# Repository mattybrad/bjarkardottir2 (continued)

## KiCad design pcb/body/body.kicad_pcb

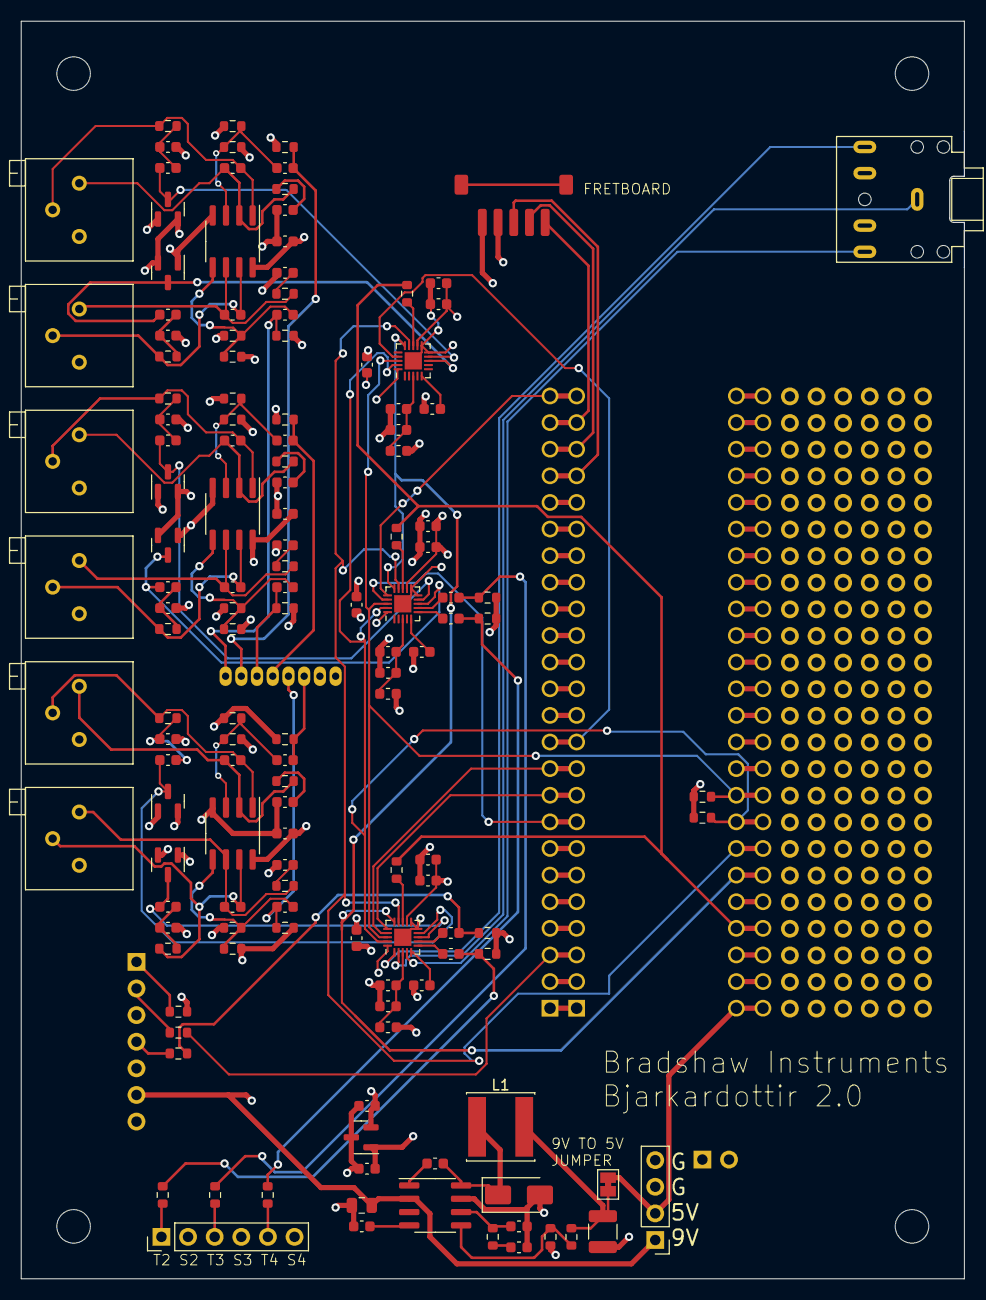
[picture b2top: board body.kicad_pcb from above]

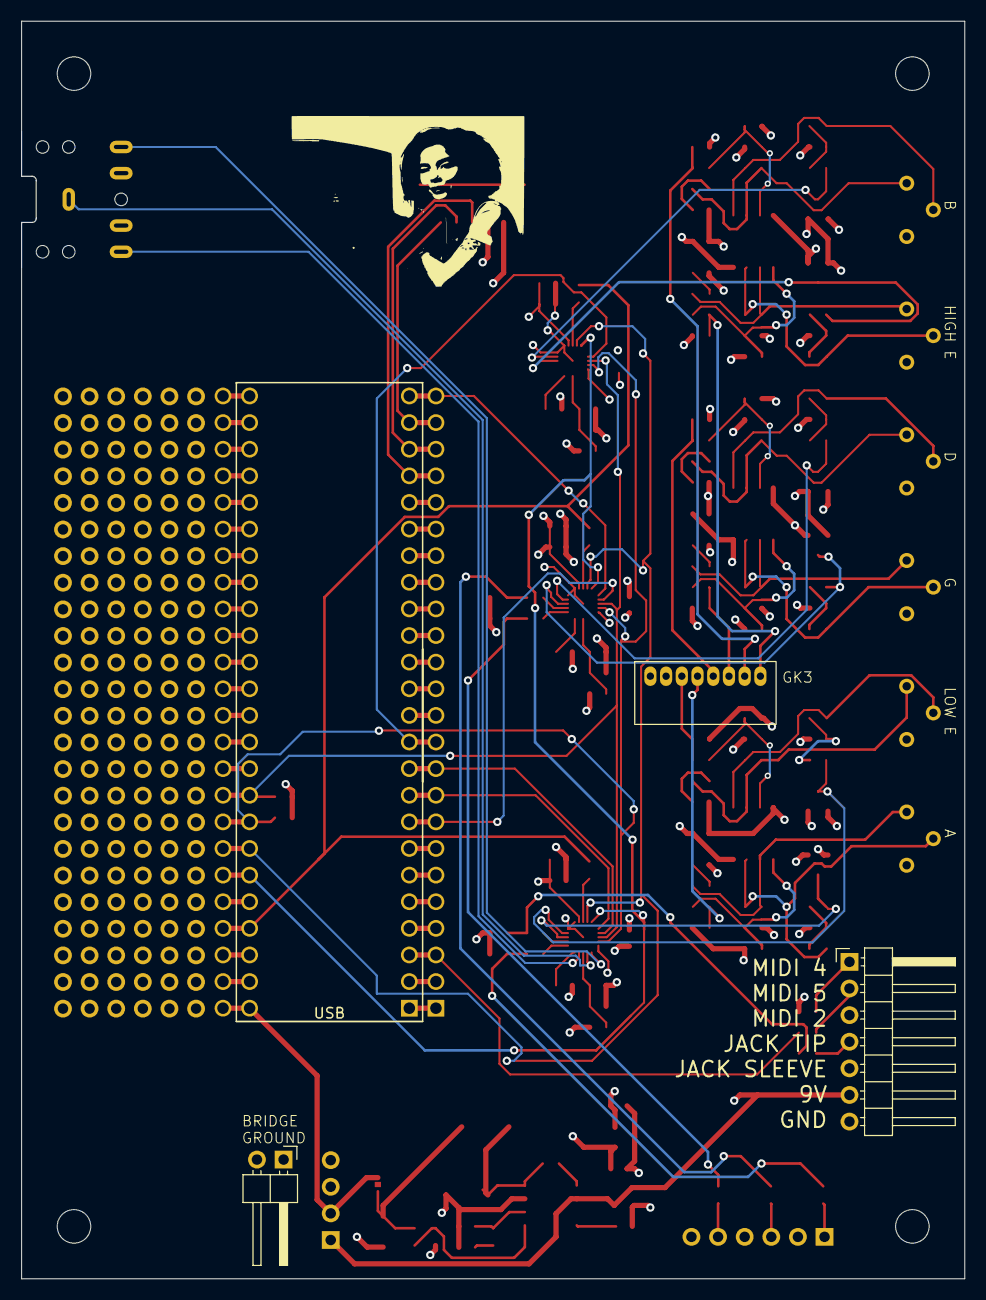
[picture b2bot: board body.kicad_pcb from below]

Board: 4 copper layers, 90.0 x 120.0 mm, 293 parts (4 on the bottom side), 94 nets.

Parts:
C1, C2, C3, C4: 1uF; C_0603_1608Metric
C5, C6, C16, C17, C27, C28: 0.1u; C_0603_1608Metric
C7, C8, C18, C19, C29, C30: 10u; C_0603_1608Metric
C9, C10, C20, C21, C31, C32: 18p; C_0603_1608Metric
C11, C22, C33: 100n; C_0603_1608Metric
C12, C13, C23, C24, C34, C35: 1n; C_0603_1608Metric
C14, C15, C25, C26, C36, C37, C60, C62: 1u; C_0603_1608Metric
C38, C40, C42, C44, C46, C48, C50, C52, C54: 2.2uF; C_0603_1608Metric
C39, C43, C45, C49, C51, C55: 0.1uF; C_0603_1608Metric
C41, C47, C53: 0.15uF; C_0603_1608Metric
C56: 22uF 16V; C_0805_2012Metric
C57: 100nF; C_0603_1608Metric
C58: 10nF; C_0603_1608Metric
C59: 1nF; C_0603_1608Metric
C61: 10pF; C_0603_1608Metric
C63: 47uF; C_1210_3225Metric
D1, D2, D3, D4, D5, D6: BAT54S; SOT-23
D7: B340A; D_SMA
FB1, FB2, FB3: 600; L_0603_1608Metric
H1, H2, H3, H4: MountingHole; MountingHole_3.2mm_M3
J1: FRETBOARD_CONNECTION; jst zh fretboard connector
J2: BRIDGE_GROUND; PinHeader_1x02_P2.54mm_Horizontal
J3: GK3_socket; gk3 connector THT
J4: AudioJack3_SwitchTR; Jack_3.5mm_CUI_SJ1-3525N_Horizontal
J5: External_connections; PinHeader_1x07_P2.54mm_Horizontal
J6: OUTPUTS_234; PinHeader_1x06_P2.54mm_Vertical
J7: Battery_Power; PinHeader_1x04_P2.54mm_Vertical
JP1: Jumper_2_Bridged; SolderJumper-2_P1.3mm_Bridged_Pad1.0x1.5mm
L1: 6.8uH; L_Sunlord_SWPA6045S
PB1, PB2, PB3, PB4, PB5, PB6, PB7, PB8, PB9, PB10, PB11, PB12, PB13, PB14, PB15, PB16, PB17, PB18, PB19, PB20, PB21, PB22, PB23, PB24, PB25, PB26, PB27, PB28, PB29, PB30, PB31, PB32, PB33, PB34, PB35, PB36, PB37, PB38, PB39, PB40, PB41, PB42, PB43, PB44, PB45, PB46, PB47, PB48, PB49, PB50, PB51, PB52, PB53, PB54, PB55, PB56, PB57, PB58, PB59, PB60, PB61, PB62, PB63, PB64, PB65, PB66, PB67, PB68, PB69, PB70, PB71, PB72, PB73, PB74, PB75, PB76, PB77, PB78, PB79, PB80, PB81, PB82, PB83, PB84, PB85, PB86, PB87, PB88, PB89, PB90, PB91, PB92, PB93, PB94, PB95, PB96, PB97, PB98, PB99, PB100, PB101, PB102, PB103, PB104, PB105, PB106, PB107, PB108, PB109, PB110, PB111, PB112, PB113, PB114, PB115, PB116, PB117, PB118, PB119, PB120, PB121, PB122, PB123, PB124, PB125, PB126, PB127, PB128, PB129, PB130, PB131, PB132, PB133, PB134, PB135, PB136, PB137, PB138, PB139, PB140, PB141, PB142, PB143, PB144: perfboard_pin; perfboard pin
R1, R2: 2.2k; R_0603_1608Metric
R3, R4, R6, R7: 47k; R_0603_1608Metric
R5, R8: 47R; R_0603_1608Metric
R9, R10, R11, R12: 100R; R_0603_1608Metric
R13, R14, R23, R24, R33, R34: 1M; R_0603_1608Metric
R15, R16, R17, R18, R25, R26, R27, R28, R35, R36, R37, R38: 2M; R_0603_1608Metric
R19, R20, R29, R30, R39, R40, R47: 10k; R_0603_1608Metric
R21, R22, R31, R32, R41, R42: 1k; R_0603_1608Metric
R43, R44, R45: 100; R_0603_1608Metric
R46: 50k; R_0603_1608Metric
R48: 1.8k; R_0603_1608Metric
RV1, RV2, RV3, RV4, RV5, RV6: 10k; Potentiometer_Bourns_3296P_Horizontal
U1: Teensy4.1; Teensy41_breakout
U2, U3, U4: TL072; SOIC-8_3.9x4.9mm_P1.27mm
U5, U6, U7: SGTL5000XNLA3; QFN-20-1EP_3x3mm_P0.4mm_EP1.65x1.65mm
U8: TPS54331DR; SOIC-8_3.9x4.9mm_P1.27mm
U9: AP7313-18SAG; SOT-23

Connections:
+1V8: C40.1, C46.1, C52.1, C62.1, U5.20 (VDDD), U6.20 (VDDD), U7.20 (VDDD), U9.2 (VO)
+3.3V: C38.1, C39.1, C44.1, C45.1, C50.1, C51.1, C60.1, D1.2 (K), D2.2 (K), D3.2 (K), D4.2 (K), D5.2 (K), D6.2 (K), FB1.1, FB2.1, FB3.1, J1.1, R1.2, R2.2, R5.1, U1.15 (3V3), U1.46 (3V3), U5.12 (VDDIO), U6.12 (VDDIO), U7.12 (VDDIO), U9.1 (VI)
+5V: J7.2, JP1.2 (B), U1.48 (VIN)
+9V: C11.2, C22.2, C33.2, C56.1, J5.6, J7.1, R15.1, R17.1, R25.1, R27.1, R35.1, R37.1, U2.8 (V+), U3.8 (V+), U4.8 (V+), U8.2 (VIN)
/MIDI_PIN_4: J5.1, R5.2
/MIDI_PIN_5: J5.2, R8.2
/codec1/HEADPHONES_GND: J4.S, U5.2 (HP_VGND)
/codec1/HEADPHONES_L: J4.T, U5.1 (HP_R)
/codec1/HEADPHONES_R: J4.R, U5.4 (HP_L)
/codec1/LINE_IN_L: C14.1, D1.3 (COM), U5.9 (LINEIN_L)
/codec1/LINE_IN_R: C15.1, D2.3 (COM), U5.8 (LINEIN_R)
/codec1/LINE_OUT_L: C1.1, U5.7 (LINEOUT_L)
/codec1/LINE_OUT_R: C2.1, U5.6 (LINEOUT_R)
/codec2/LINE_IN_L: C25.1, D3.3 (COM), U6.9 (LINEIN_L)
/codec2/LINE_IN_R: C26.1, D4.3 (COM), U6.8 (LINEIN_R)
/codec2/LINE_OUT_L: C3.1, U6.7 (LINEOUT_L)
/codec2/LINE_OUT_R: C4.1, U6.6 (LINEOUT_R)
/codec3/LINE_IN_L: C36.1, D5.3 (COM), U7.9 (LINEIN_L)
/codec3/LINE_IN_R: C37.1, D6.3 (COM), U7.8 (LINEIN_R)
/pickuppair1/INPUT_1: C5.1, J3.3, R13.1
/pickuppair1/INPUT_2: C6.1, J3.4, R14.1
/pickuppair2/INPUT_1: C16.1, J3.5, R23.1
/pickuppair2/INPUT_2: C17.1, J3.6, R24.1
/pickuppair3/INPUT_1: C27.1, J3.7, R33.1
/pickuppair3/INPUT_2: C28.1, J3.8, R34.1
CODEC1_DIN: U1.10 (8_TX2_IN1), U5.17 (I2S_DIN)
CODEC1_DOUT: U1.9 (7_RX2_OUT1A), U5.16 (I2S_DOUT)
CODEC2_DIN: U1.8 (6_OUT1D), U6.17 (I2S_DIN)
CODEC2_DOUT: U1.24 (32_OUT1B), U6.16 (I2S_DOUT)
CODEC3_DIN: U1.11 (9_OUT1C), U7.17 (I2S_DIN)
DAC_BCLK: U1.43 (21_A7_RX5_BCLK1), U5.15 (I2S_SCLK), U6.15 (I2S_SCLK), U7.15 (I2S_SCLK)
DAC_LRCLK: U1.42 (20_A6_TX5_LRCLK1), U5.14 (I2S_LRCLK), U6.14 (I2S_LRCLK), U7.14 (I2S_LRCLK)
DAC_MCLK: R43.2, R44.2, R45.2, U1.45 (23_A9_CRX1_MCLK1)
DAC_SCL: R1.1, U1.41 (19_A5_SCL), U5.19 (CTRL_CLK), U6.19 (CTRL_CLK), U7.19 (CTRL_CLK)
DAC_SDA: R2.1, U1.40 (18_A4_SDA), U5.18 (CTRL_DATA), U6.18 (CTRL_DATA), U7.18 (CTRL_DATA)
FRET_CLOCK: J1.3, U1.21 (29_TX7)
FRET_DATA: J1.5, U1.23 (31_CTX3)
FRET_LOAD: J1.4, U1.22 (30_CRX3)
GND: C7.1, C8.1, C11.1, C12.2, C13.2, C18.1, C19.1, C22.1, C23.2, C24.2, C29.1, C30.1, C33.1, C34.2, C35.2, C38.2, C39.2, C40.2, C41.2, C42.2, C43.2, C44.2, C45.2, C46.2, C47.2, C48.2, C49.2, C50.2, C51.2, C52.2, C53.2, C54.2, C55.2, C56.2, C58.2, C59.2, C60.2, C61.2, C62.2, C63.2, D1.1 (A), D2.1 (A), D3.1 (A), D4.1 (A), D5.1 (A), D6.1 (A), D7.2 (A), J1.2, J2.1, J2.2, J3.1, J3.2, J5.3, J5.5, J5.7, J6.2, J6.4, J6.6, J7.3, J7.4, R3.1, R4.1, R6.1, R7.1, R13.2, R14.2, R16.2, R18.2, R23.2, R24.2, R26.2, R28.2, R33.2, R34.2, R36.2, R38.2, R48.2, U1.1 (GND), U1.34 (GND), U1.47 (GND), U2.4 (V-), U3.4 (V-), U4.4 (V-), U5.10 (MIC), U5.11 (MIC_BIAS), U5.21 (GND), U6.10 (MIC), U6.11 (MIC_BIAS), U6.21 (GND), U7.10 (MIC), U7.11 (MIC_BIAS), U7.21 (GND), U8.7 (GND), U9.3 (GND)
MAIN_OUTPUT: J5.4, R9.1
MIDI_OUT: R8.1, U1.3 (1_TX1_CTX2_MISO1)
unnamed: C1.2, R6.2, R9.2
unnamed: C2.2, R3.2, R10.2
unnamed: C3.2, R7.2, R11.2
unnamed: C4.2, R4.2, R12.2
unnamed: C7.2, R19.1
unnamed: C8.2, R20.1
unnamed: C9.2, R21.1, RV1.2, U2.1
unnamed: C10.2, R22.1, RV2.2, U2.7
unnamed: C12.1, C14.2, R21.2
unnamed: C13.1, C15.2, R22.2
unnamed: C18.2, R29.1
unnamed: C19.2, R30.1
unnamed: C20.2, R31.1, RV3.2, U3.1
unnamed: C21.2, R32.1, RV4.2, U3.7
unnamed: C23.1, C25.2, R31.2
unnamed: C24.1, C26.2, R32.2
unnamed: C29.2, R39.1
unnamed: C30.2, R40.1
unnamed: C31.2, R41.1, RV5.2, U4.1
unnamed: C32.2, R42.1, RV6.2, U4.7
unnamed: C34.1, C36.2, R41.2
unnamed: C35.1, C37.2, R42.2
unnamed: C59.1, R46.2
unnamed: C57.1, D7.1 (K), L1.1, U8.8 (PH)
unnamed: J6.1, R10.1
unnamed: J6.3, R11.1
unnamed: J6.5, R12.1
unnamed: C63.1, JP1.1 (A), L1.2, R47.1
unnamed: C5.2, R15.2, R16.1, U2.3 (+)
unnamed: C9.1, R19.2, RV1.1, U2.2 (-)
unnamed: C6.2, R17.2, R18.1, U2.5 (+)
unnamed: C10.1, R20.2, RV2.1, U2.6 (-)
unnamed: C16.2, R25.2, R26.1, U3.3 (+)
unnamed: C20.1, R29.2, RV3.1, U3.2 (-)
unnamed: C17.2, R27.2, R28.1, U3.5 (+)
unnamed: C21.1, R30.2, RV4.1, U3.6 (-)
unnamed: C27.2, R35.2, R36.1, U4.3 (+)
unnamed: C31.1, R39.2, RV5.1, U4.2 (-)
unnamed: C28.2, R37.2, R38.1, U4.5 (+)
unnamed: C32.1, R40.2, RV6.1, U4.6 (-)
unnamed: R43.1, U5.13 (SYS_MCLK)
unnamed: C41.1, U5.5 (VAG)
unnamed: C42.1, C43.1, FB1.2, U5.3 (VDDA)
unnamed: R44.1, U6.13 (SYS_MCLK)
unnamed: C47.1, U6.5 (VAG)
unnamed: C48.1, C49.1, FB2.2, U6.3 (VDDA)
unnamed: R45.1, U7.13 (SYS_MCLK)
unnamed: C53.1, U7.5 (VAG)
unnamed: C54.1, C55.1, FB3.2, U7.3 (VDDA)
unnamed: C57.2, U8.1 (BOOT)
unnamed: C61.1, R46.1, U8.6 (COMP)
unnamed: C58.1, U8.4 (SS)
unnamed: R47.2, R48.1, U8.5 (VSENSE)

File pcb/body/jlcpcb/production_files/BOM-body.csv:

Comment,Designator,Footprint,LCSC
600,"FB1,FB2,FB3",L_0603_1608Metric,C1002
100n,"C11,C16,C17,C22,C27,C28,C33,C39,C43,C45,C49,C5,C51,C55,C57,C6",C_0603_1608Metric,C14663
1uF,"C1,C14,C15,C2,C25,C26,C3,C36,C37,C4,C60,C62",C_0603_1608Metric,C15849
1n,"C12,C13,C23,C24,C34,C35,C59",C_0603_1608Metric,C1588
10nF,"C58,C61",C_0603_1608Metric,C1634
18p,"C10,C20,C21,C31,C32,C9",C_0603_1608Metric,C1647
1k,"R21,R22,R31,R32,R41,R42",R_0603_1608Metric,C21190
100R,"R10,R11,R12,R43,R44,R45,R9",R_0603_1608Metric,C22775
1M,"R13,R14,R23,R24,R33,R34",R_0603_1608Metric,C22935
2M,"R15,R16,R17,R18,R25,R26,R27,R28,R35,R36,R37,R38",R_0603_1608Metric,C22976
47R,"R5,R8",R_0603_1608Metric,C23182
50k,R46,R_0603_1608Metric,C23184
2.2uF,"C38,C40,C42,C44,C46,C48,C50,C52,C54",C_0603_1608Metric,C23630
10k,"R19,R20,R29,R30,R39,R40,R47",R_0603_1608Metric,C25804
47k,"R3,R4,R6,R7",R_0603_1608Metric,C25819
SGTL5000XNLA3,"U5,U6,U7",QFN-20-1EP_3x3mm_P0.4mm_EP1.65x1.65mm,C2651833
B340A,D7,D_SMA,C3018525
1.8k,R48,R_0603_1608Metric,C4177
2.2k,"R1,R2",R_0603_1608Metric,C4190
22uF 16V,C56,C_0805_2012Metric,C45783
AP7313-18SAG,U9,SOT-23,C460373
FRETBOARD_CONNECTION,J1,jst zh fretboard connector,C485355
0.15uF,"C41,C47,C53",C_0603_1608Metric,C513735
6.8uH,L1,L_Sunlord_SWPA6045S,C57254
TL072,"U2,U3,U4",SOIC-8_3.9x4.9mm_P1.27mm,C6961
47uF,C63,C_1210_3225Metric,C89147
BAT54S,"D1,D2,D3,D4,D5,D6",SOT-23,C916425
10u,"C18,C19,C29,C30,C7,C8",C_0603_1608Metric,C96446
TPS54331DR,U8,SOIC-8_3.9x4.9mm_P1.27mm,C9865
perfboard_pin,PB144,perfboard pin,
perfboard_pin,PB143,perfboard pin,
perfboard_pin,PB142,perfboard pin,
perfboard_pin,PB141,perfboard pin,
perfboard_pin,PB140,perfboard pin,
perfboard_pin,PB139,perfboard pin,
perfboard_pin,PB138,perfboard pin,
perfboard_pin,PB137,perfboard pin,
perfboard_pin,PB136,perfboard pin,
perfboard_pin,PB135,perfboard pin,
perfboard_pin,PB134,perfboard pin,
perfboard_pin,PB133,perfboard pin,
perfboard_pin,PB132,perfboard pin,
perfboard_pin,PB131,perfboard pin,
perfboard_pin,PB130,perfboard pin,
perfboard_pin,PB129,perfboard pin,
perfboard_pin,PB128,perfboard pin,
perfboard_pin,PB127,perfboard pin,
perfboard_pin,PB126,perfboard pin,
perfboard_pin,PB125,perfboard pin,
perfboard_pin,PB124,perfboard pin,
perfboard_pin,PB123,perfboard pin,
perfboard_pin,PB122,perfboard pin,
perfboard_pin,PB121,perfboard pin,
perfboard_pin,PB120,perfboard pin,
perfboard_pin,PB119,perfboard pin,
perfboard_pin,PB118,perfboard pin,
perfboard_pin,PB117,perfboard pin,
perfboard_pin,PB116,perfboard pin,
perfboard_pin,PB115,perfboard pin,
perfboard_pin,PB114,perfboard pin,
perfboard_pin,PB113,perfboard pin,
perfboard_pin,PB112,perfboard pin,
perfboard_pin,PB111,perfboard pin,
perfboard_pin,PB110,perfboard pin,
perfboard_pin,PB109,perfboard pin,
perfboard_pin,PB108,perfboard pin,
perfboard_pin,PB107,perfboard pin,
perfboard_pin,PB106,perfboard pin,
perfboard_pin,PB105,perfboard pin,
perfboard_pin,PB104,perfboard pin,
perfboard_pin,PB103,perfboard pin,
perfboard_pin,PB102,perfboard pin,
perfboard_pin,PB101,perfboard pin,
perfboard_pin,PB100,perfboard pin,
perfboard_pin,PB99,perfboard pin,
perfboard_pin,PB98,perfboard pin,
perfboard_pin,PB97,perfboard pin,
perfboard_pin,PB96,perfboard pin,
perfboard_pin,PB95,perfboard pin,
perfboard_pin,PB94,perfboard pin,
perfboard_pin,PB93,perfboard pin,
perfboard_pin,PB92,perfboard pin,
perfboard_pin,PB91,perfboard pin,
perfboard_pin,PB90,perfboard pin,
perfboard_pin,PB89,perfboard pin,
perfboard_pin,PB88,perfboard pin,
perfboard_pin,PB87,perfboard pin,
perfboard_pin,PB86,perfboard pin,
perfboard_pin,PB85,perfboard pin,
perfboard_pin,PB84,perfboard pin,
perfboard_pin,PB83,perfboard pin,
perfboard_pin,PB82,perfboard pin,
perfboard_pin,PB81,perfboard pin,
perfboard_pin,PB80,perfboard pin,
perfboard_pin,PB79,perfboard pin,
perfboard_pin,PB78,perfboard pin,
perfboard_pin,PB77,perfboard pin,
perfboard_pin,PB76,perfboard pin,
perfboard_pin,PB75,perfboard pin,
perfboard_pin,PB74,perfboard pin,
perfboard_pin,PB73,perfboard pin,
perfboard_pin,PB72,perfboard pin,
perfboard_pin,PB71,perfboard pin,
perfboard_pin,PB70,perfboard pin,
perfboard_pin,PB69,perfboard pin,
perfboard_pin,PB68,perfboard pin,
perfboard_pin,PB67,perfboard pin,
perfboard_pin,PB66,perfboard pin,
perfboard_pin,PB65,perfboard pin,
perfboard_pin,PB64,perfboard pin,
perfboard_pin,PB63,perfboard pin,
perfboard_pin,PB62,perfboard pin,
perfboard_pin,PB61,perfboard pin,
perfboard_pin,PB60,perfboard pin,
perfboard_pin,PB59,perfboard pin,
perfboard_pin,PB58,perfboard pin,
perfboard_pin,PB57,perfboard pin,
perfboard_pin,PB56,perfboard pin,
perfboard_pin,PB55,perfboard pin,
perfboard_pin,PB54,perfboard pin,
perfboard_pin,PB53,perfboard pin,
perfboard_pin,PB52,perfboard pin,
perfboard_pin,PB51,perfboard pin,
perfboard_pin,PB50,perfboard pin,
perfboard_pin,PB49,perfboard pin,
perfboard_pin,PB48,perfboard pin,
perfboard_pin,PB47,perfboard pin,
perfboard_pin,PB46,perfboard pin,
perfboard_pin,PB45,perfboard pin,
perfboard_pin,PB44,perfboard pin,
perfboard_pin,PB43,perfboard pin,
perfboard_pin,PB42,perfboard pin,
perfboard_pin,PB41,perfboard pin,
perfboard_pin,PB40,perfboard pin,
perfboard_pin,PB39,perfboard pin,
perfboard_pin,PB38,perfboard pin,
perfboard_pin,PB37,perfboard pin,
perfboard_pin,PB36,perfboard pin,
perfboard_pin,PB35,perfboard pin,
perfboard_pin,PB34,perfboard pin,
perfboard_pin,PB33,perfboard pin,
perfboard_pin,PB32,perfboard pin,
perfboard_pin,PB31,perfboard pin,
perfboard_pin,PB30,perfboard pin,
perfboard_pin,PB29,perfboard pin,
perfboard_pin,PB28,perfboard pin,
perfboard_pin,PB27,perfboard pin,
perfboard_pin,PB26,perfboard pin,
perfboard_pin,PB25,perfboard pin,
perfboard_pin,PB24,perfboard pin,
perfboard_pin,PB23,perfboard pin,
perfboard_pin,PB22,perfboard pin,
perfboard_pin,PB21,perfboard pin,
perfboard_pin,PB20,perfboard pin,
perfboard_pin,PB19,perfboard pin,
perfboard_pin,PB18,perfboard pin,
perfboard_pin,PB17,perfboard pin,
perfboard_pin,PB16,perfboard pin,
perfboard_pin,PB15,perfboard pin,
perfboard_pin,PB14,perfboard pin,
perfboard_pin,PB13,perfboard pin,
perfboard_pin,PB12,perfboard pin,
perfboard_pin,PB11,perfboard pin,
perfboard_pin,PB10,perfboard pin,
perfboard_pin,PB9,perfboard pin,
perfboard_pin,PB8,perfboard pin,
perfboard_pin,PB7,perfboard pin,
perfboard_pin,PB6,perfboard pin,
perfboard_pin,PB5,perfboard pin,
perfboard_pin,PB4,perfboard pin,
perfboard_pin,PB3,perfboard pin,
perfboard_pin,PB2,perfboard pin,
perfboard_pin,PB1,perfboard pin,
GK3_socket,J3,gk3 connector THT,
Jumper_2_Bridged,JP1,SolderJumper-2_P1.3mm_Bridged_Pad1.0x1.5mm,
10k,RV6,Potentiometer_Bourns_3296P_Horizontal,
OUTPUTS_234,J6,PinHeader_1x06_P2.54mm_Vertical,
Battery_Power,J7,PinHeader_1x04_P2.54mm_Vertical,
MountingHole,H3,MountingHole_3.2mm_M3,
10k,RV4,Potentiometer_Bourns_3296P_Horizontal,
MountingHole,H1,MountingHole_3.2mm_M3,
10k,RV1,Potentiometer_Bourns_3296P_Horizontal,
10k,RV3,Potentiometer_Bourns_3296P_Horizontal,
10k,RV2,Potentiometer_Bourns_3296P_Horizontal,
MountingHole,H4,MountingHole_3.2mm_M3,
10k,RV5,Potentiometer_Bourns_3296P_Horizontal,
MountingHole,H2,MountingHole_3.2mm_M3,
AudioJack3_SwitchTR,J4,Jack_3.5mm_CUI_SJ1-3525N_Horizontal,
External_connections,J5,PinHeader_1x07_P2.54mm_Horizontal,
BRIDGE_GROUND,J2,PinHeader_1x02_P2.54mm_Horizontal,
Teensy4.1,U1,Teensy41_breakout,

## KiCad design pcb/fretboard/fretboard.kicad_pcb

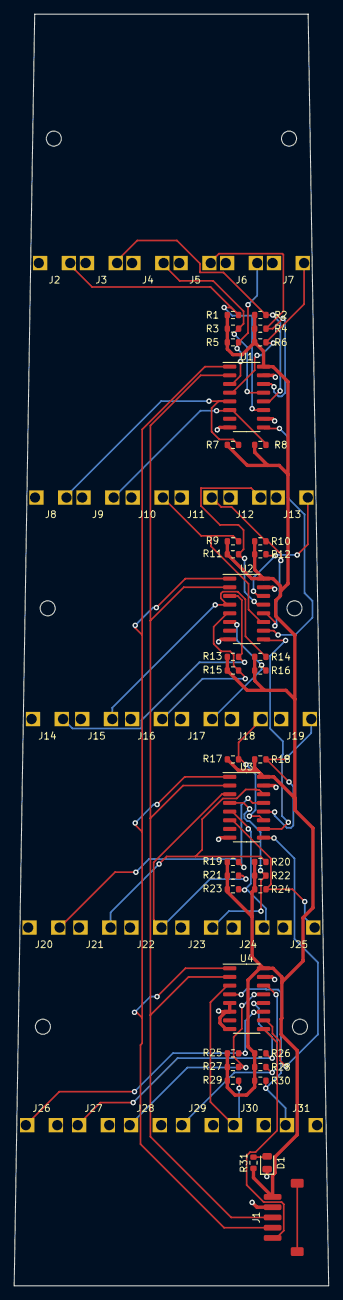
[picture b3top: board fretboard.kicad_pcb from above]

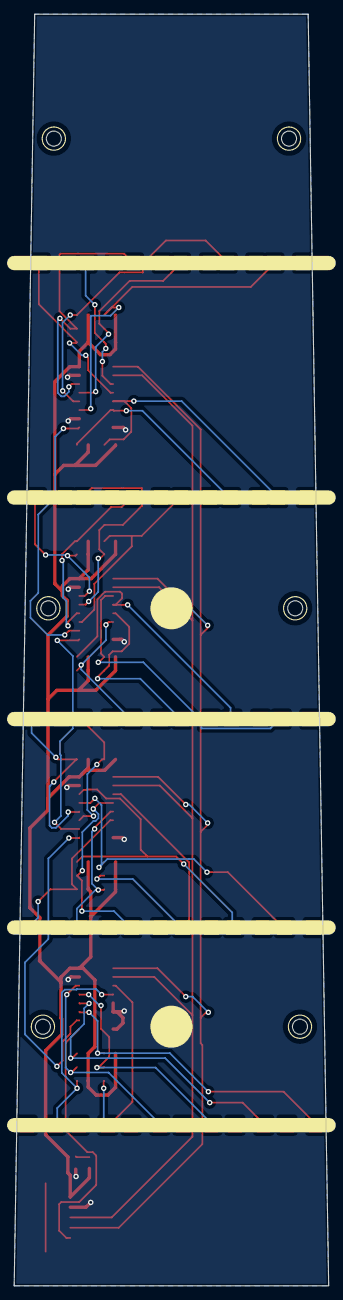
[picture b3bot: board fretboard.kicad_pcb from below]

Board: 2 copper layers, 46.0 x 186.0 mm, 73 parts (6 on the bottom side), 39 nets.

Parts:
D1: LED; LED_0805_2012Metric
H1, H2, H3, H4, H5, H6: MountingHole; MountingHole_2.2mm_M2_countersunk
J1: Conn_01x06_Pin; jst zh fretboard connector
J2, J3, J4, J5, J6, J7, J8, J9, J10, J11, J12, J13, J14, J15, J16, J17, J18, J19, J20, J21, J22, J23, J24, J25, J26, J27, J28, J29, J30, J31: Conn_01x01_Pin; Bjarkar_fret_connection
R1, R2, R3, R4, R5, R6, R7, R8, R9, R10, R11, R12, R13, R14, R15, R16, R17, R18, R19, R20, R21, R22, R23, R24, R25, R26, R27, R28, R29, R30: 10k; R_0603_1608Metric
R31: 220R; R_0603_1608Metric
U1, U2, U3, U4: 74HC165; SOIC-16_3.9x9.9mm_P1.27mm

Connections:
165_CLOCK: J1.3, U1.2 (CP), U2.2 (CP), U3.2 (CP), U4.2 (CP)
165_LOAD: J1.4, U1.1 (~PL), U2.1 (~PL), U3.1 (~PL), U4.1 (~PL)
+3.3V: J1.1, R1.1, R2.1, R3.1, R4.1, R5.1, R6.1, R7.1, R8.1, R9.1, R10.1, R11.1, R12.1, R13.1, R14.1, R15.1, R16.1, R17.1, R18.1, R19.1, R20.1, R21.1, R22.1, R23.1, R24.1, R25.1, R26.1, R27.1, R28.1, R29.1, R30.1, R31.1, U1.16 (VCC), U2.16 (VCC), U3.16 (VCC), U4.16 (VCC)
/ShiftReg1/DATA_OUT: U1.9 (Q7), U2.10 (DS)
/ShiftReg2/DATA_OUT: U2.9 (Q7), U3.10 (DS)
/ShiftReg3/DATA_OUT: U3.9 (Q7), U4.10 (DS)
/ShiftReg4/DATA_OUT: J1.5, U4.9 (Q7)
GND: D1.1 (K), J1.2, U1.8 (GND), U1.10 (DS), U1.15 (~CE), U2.8 (GND), U2.15 (~CE), U3.8 (GND), U3.15 (~CE), U4.5 (D6), U4.6 (D7), U4.8 (GND), U4.15 (~CE)
unnamed: D1.2 (A), R31.2
unnamed: J2.1, R1.2, U1.11 (D0)
unnamed: J3.1, R2.2, U1.12 (D1)
unnamed: J4.1, R3.2, U1.13 (D2)
unnamed: J5.1, R4.2, U1.14 (D3)
unnamed: J6.1, R5.2, U1.3 (D4)
unnamed: J7.1, R6.2, U1.4 (D5)
unnamed: J8.1, R7.2, U1.5 (D6)
unnamed: J9.1, R8.2, U1.6 (D7)
unnamed: J10.1, R9.2, U2.11 (D0)
unnamed: J11.1, R10.2, U2.12 (D1)
unnamed: J12.1, R11.2, U2.13 (D2)
unnamed: J13.1, R12.2, U2.14 (D3)
unnamed: J14.1, R13.2, U2.3 (D4)
unnamed: J15.1, R14.2, U2.4 (D5)
unnamed: J16.1, R15.2, U2.5 (D6)
unnamed: J17.1, R16.2, U2.6 (D7)
unnamed: J18.1, R17.2, U3.11 (D0)
unnamed: J19.1, R18.2, U3.12 (D1)
unnamed: J20.1, R19.2, U3.13 (D2)
unnamed: J21.1, R20.2, U3.14 (D3)
unnamed: J22.1, R21.2, U3.3 (D4)
unnamed: J23.1, R22.2, U3.4 (D5)
unnamed: J24.1, R23.2, U3.5 (D6)
unnamed: J25.1, R24.2, U3.6 (D7)
unnamed: J26.1, R25.2, U4.11 (D0)
unnamed: J27.1, R26.2, U4.12 (D1)
unnamed: J28.1, R27.2, U4.13 (D2)
unnamed: J29.1, R28.2, U4.14 (D3)
unnamed: J30.1, R29.2, U4.3 (D4)
unnamed: J31.1, R30.2, U4.4 (D5)

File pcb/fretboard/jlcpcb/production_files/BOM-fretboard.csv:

Comment,Designator,Footprint,LCSC
220R,R31,R_0603_1608Metric,C22962
LED,D1,LED_0805_2012Metric,C2297
10k,"R1,R10,R11,R12,R13,R14,R15,R16,R17,R18,R19,R2,R20,R21,R22,R23,R24,R25,R26,R27,R28,R29,R3,R30,R4,R5,R6,R7,R8,R9",R_0603_1608Metric,C25804
Conn_01x06_Pin,J1,jst zh fretboard connector,C485355
74HC165,"U1,U2,U3,U4",SOIC-16_3.9x9.9mm_P1.27mm,C5613
Conn_01x01_Pin,J31,Bjarkar_fret_connection,
Conn_01x01_Pin,J30,Bjarkar_fret_connection,
Conn_01x01_Pin,J29,Bjarkar_fret_connection,
Conn_01x01_Pin,J28,Bjarkar_fret_connection,
Conn_01x01_Pin,J27,Bjarkar_fret_connection,
Conn_01x01_Pin,J26,Bjarkar_fret_connection,
Conn_01x01_Pin,J10,Bjarkar_fret_connection,
Conn_01x01_Pin,J19,Bjarkar_fret_connection,
Conn_01x01_Pin,J2,Bjarkar_fret_connection,
Conn_01x01_Pin,J22,Bjarkar_fret_connection,
Conn_01x01_Pin,J8,Bjarkar_fret_connection,
Conn_01x01_Pin,J15,Bjarkar_fret_connection,
Conn_01x01_Pin,J20,Bjarkar_fret_connection,
Conn_01x01_Pin,J25,Bjarkar_fret_connection,
Conn_01x01_Pin,J4,Bjarkar_fret_connection,
Conn_01x01_Pin,J24,Bjarkar_fret_connection,
Conn_01x01_Pin,J6,Bjarkar_fret_connection,
Conn_01x01_Pin,J7,Bjarkar_fret_connection,
Conn_01x01_Pin,J23,Bjarkar_fret_connection,
Conn_01x01_Pin,J5,Bjarkar_fret_connection,
Conn_01x01_Pin,J21,Bjarkar_fret_connection,
Conn_01x01_Pin,J18,Bjarkar_fret_connection,
Conn_01x01_Pin,J12,Bjarkar_fret_connection,
Conn_01x01_Pin,J11,Bjarkar_fret_connection,
Conn_01x01_Pin,J3,Bjarkar_fret_connection,
Conn_01x01_Pin,J16,Bjarkar_fret_connection,
Conn_01x01_Pin,J9,Bjarkar_fret_connection,
Conn_01x01_Pin,J17,Bjarkar_fret_connection,
Conn_01x01_Pin,J14,Bjarkar_fret_connection,
Conn_01x01_Pin,J13,Bjarkar_fret_connection,
MountingHole,H5,MountingHole_2.2mm_M2_countersunk,
MountingHole,H2,MountingHole_2.2mm_M2_countersunk,
MountingHole,H3,MountingHole_2.2mm_M2_countersunk,
MountingHole,H1,MountingHole_2.2mm_M2_countersunk,
MountingHole,H4,MountingHole_2.2mm_M2_countersunk,
MountingHole,H6,MountingHole_2.2mm_M2_countersunk,

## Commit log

2024-11-12 here we go again
2024-11-12 started body pcb
2024-11-19 pcb stuff
2024-11-19 output stage
2025-01-28 connector breakout
2025-01-29 linked input stages to codecs
2025-01-30 not much
2025-01-31 nice progress
2025-02-03 initial layout
2025-02-04 lots more layout
2025-02-04 more layout...
2025-02-05 haven't committed for a bit
2025-02-05 first four layer board...
2025-02-05 4 layer routing...
2025-02-07 routing going well with 4 layers
2025-02-07 zero unrouted for now
2025-02-10 getting there
2025-02-10 fretboard routing
2025-02-11 faffing with fretboard
2025-02-11 fretboard routing done
2025-02-12 fretboard finished
2025-02-14 body pcb zero errors
2025-02-14 silkscreen
2025-02-14 body pcb done
2025-02-17 body done
2025-04-16 pcb2
2025-04-18 nicer layout
2025-04-20 more layout
2025-04-20 replicate layout plugin not working
2025-04-22 kicad 9
2025-04-25 layout
2025-04-29 routing
2025-04-29 routing mainly done
2025-04-29 zero errors
2025-05-02 pcb 2 done
2025-06-07 pcb v2.1 works really well!!!
